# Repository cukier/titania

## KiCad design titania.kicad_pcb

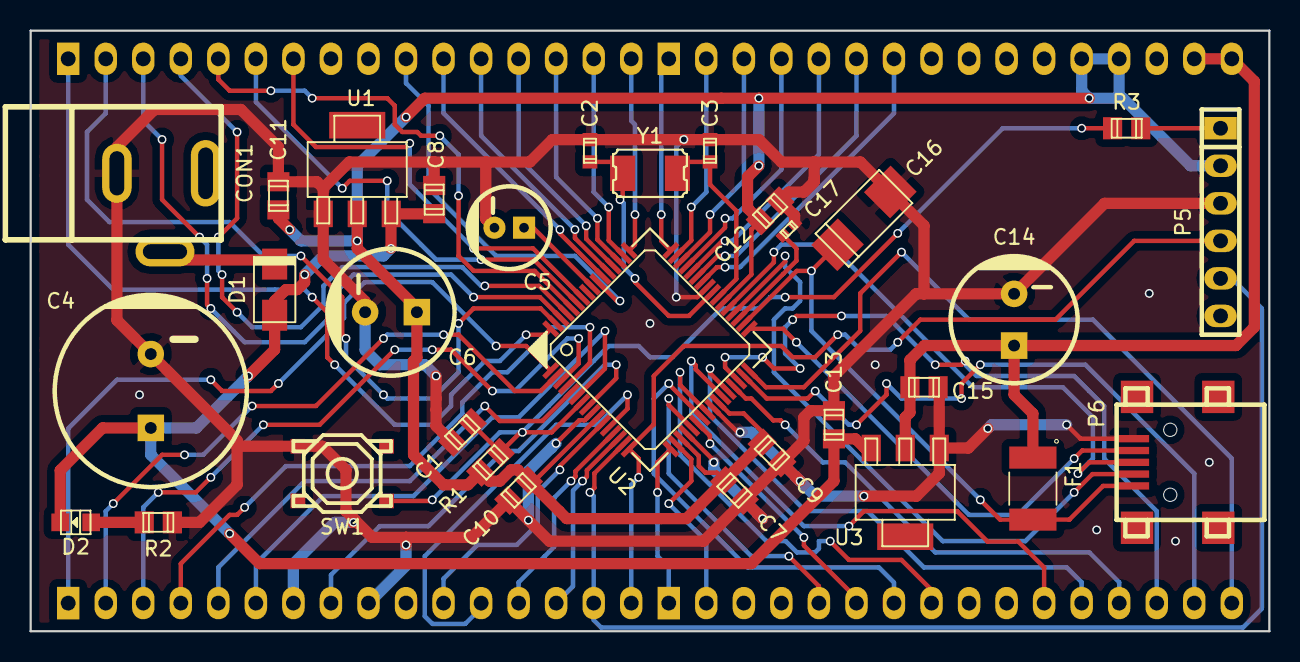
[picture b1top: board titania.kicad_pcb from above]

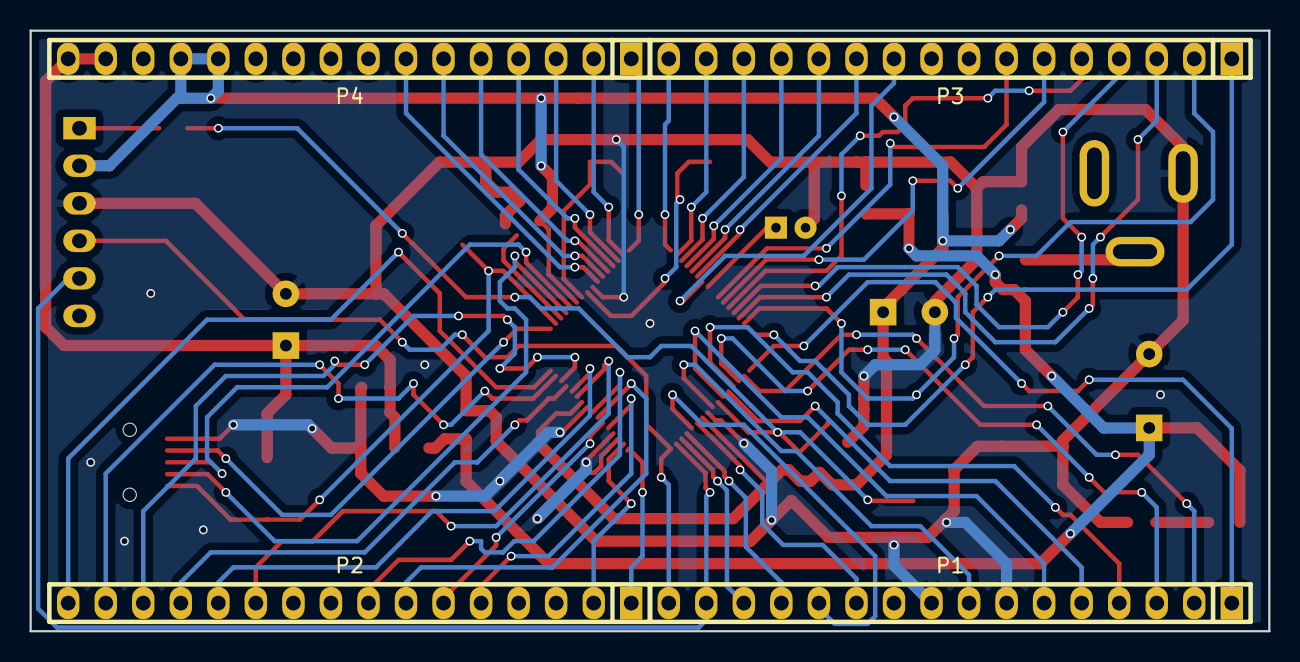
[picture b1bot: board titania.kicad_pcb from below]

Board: 2 copper layers, 83.8 x 40.6 mm, 35 parts (4 on the bottom side), 62 nets.

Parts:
C1, C5, C7, C9, C10, C11, C12, C13, C15: 100nF; c_0805
C2, C3: 22pF; c_0603
C4: 470uF 50V; CP_12.5x15mm
C6, C14: 470uF 16V; CP_8x11.5mm
C8: 10uF 16V; CP_5x11mm
C16: 150uF 6.3V; c_tant_C
C17: 0.1uF 3.3V; c_0402
CON1: BARREL_JACK; dc_socket
D1: 1n4007; do214ac
D2: LED; Led_0805
F1: F_Small; FUSM4632X85
P1, P2, P3, P4: CONN_01X16; pin_strip_16
P5: CONN_01X06; pin_strip_6
P6: USB_OTG; conn_usb_B_mini_smd
R1: 10K; r_0805
R2: 560R; r_0805
R3: 100R; r_0805
SW1: SW_PUSH; smd_push2
U1: LD1117S33TR; sot223
U2: PIC24FJ1024GB610; lqfp64
U3: LD1117S50TR; sot223
Y1: Crystal; crystal_smd_5x3.2mm

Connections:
+3.3V: C6.1, C7.1, C9.1, C10.1, C11.1, C12.1, P4.12, P4.13, P5.2, R1.1, U1.2, U2.10, U2.19, U2.26, U2.38
+5V: C14.1, C15.1, F1.1, P4.15, P4.16, U3.2
/L1: P1.1, U2.1
/L2: P1.2, U2.2
/L3: P1.3, U2.3
/L4: P1.4, U2.4
/L5: P1.5, U2.5
/L6: P1.6, U2.6
/L8: P1.8, U2.8
/L11: P1.11, U2.11
/L12: P1.12, U2.12
/L13: P1.13, U2.13
/L14: P1.14, U2.14
/L15: P1.15, P5.5, U2.15
/L16: P1.16, P5.4, U2.16
/L17: P2.1, U2.17
/L18: P2.2, U2.18
/L21: P2.5, U2.21
/L22: P2.6, U2.22
/L23: P2.7, U2.23
/L24: P2.8, U2.24
/L27: P2.11, U2.27
/L28: P2.12, U2.28
/L29: P2.13, U2.29
/L30: P2.14, U2.30
/L31: P2.15, U2.31
/L32: P2.16, U2.32
/L33: P6.4, U2.33
/L34: C16.1, F1.2, P6.1, U2.34
/L35: C17.1, U2.35
/L36: P6.2, U2.36
/L37: P6.3, U2.37
/L42: P4.7, U2.42
/L43: P4.6, U2.43
/L44: P4.5, U2.44
/L45: P4.4, U2.45
/L46: P4.3, U2.46
/L47: P4.2, U2.47
/L48: P4.1, U2.48
/L49: P3.16, U2.49
/L50: P3.15, U2.50
/L51: P3.14, U2.51
/L52: P3.13, U2.52
/L53: P3.12, U2.53
/L54: P3.11, U2.54
/L55: P3.10, U2.55
/L58: P3.7, U2.58
/L59: P3.6, U2.59
/L60: P3.5, U2.60
/L61: P3.4, U2.61
/L62: P3.3, U2.62
/L63: P3.2, U2.63
/L64: P3.1, U2.64
/MCLR: C1.1, R1.2, R3.2, SW1.1, U2.7
/OSC1: C2.1, U2.40, Y1.1
/OSC2: C3.1, U2.39, Y1.2
GND: C1.2, C2.2, C3.2, C4.2, C5.2, C6.2, C7.2, C8.2, C9.2, C10.2, C11.2, C12.2, C13.2, C14.2, C15.2, C16.2, C17.2, CON1.2, P1.7, P1.9, P5.3, P6.5, R2.2, SW1.2, U1.1, U2.9, U2.20, U2.25, U2.41, U3.1
unnamed: C8.1, U2.56
unnamed: CON1.1, D1.2
unnamed: D2.1, R2.1
unnamed: P5.1, R3.1
VCC: C4.1, C5.1, C13.1, D1.1, D2.2, U1.3, U3.3

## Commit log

2016-12-06 titania
    Adapatador pic 24f para protoboard
    +PIC24FJ1024GB610
    +LD117S33TR
    +adaptador JACK
    +Crystal
2016-12-07 entrada usb energia
2016-12-21 usb host
